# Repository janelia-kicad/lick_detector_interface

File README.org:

# Created 2021-05-14 Fri 12:59
#+OPTIONS: title:nil author:nil email:nil toc:t |:t ^:nil
* Repository Information

- Name :: lick_detector_interface
- Version :: 1.0
- License :: Open-Source Hardware
- URL :: https://github.com/janelia-kicad/lick_detector_interface
- Author :: Peter Polidoro
- Email :: peter@polidoro.io

** Description

This board connects a Teensy 4.1 to 12 lick_detector boards.

* Images

* Schematic

[[file:./schematic/lick_detector_interface.pdf][./schematic/lick_detector_interface.pdf]]

[[file:./schematic/images/schematic00.png]]

[[file:./schematic/images/schematic01.png]]

[[file:./schematic/images/schematic02.png]]

[[file:./schematic/images/schematic03.png]]

[[file:./schematic/images/schematic04.png]]

[[file:./schematic/images/schematic05.png]]

[[file:./schematic/images/schematic06.png]]

[[file:./schematic/images/schematic07.png]]

[[file:./schematic/images/schematic08.png]]

[[file:./schematic/images/schematic09.png]]

[[file:./schematic/images/schematic10.png]]

[[file:./schematic/images/schematic11.png]]

[[file:./schematic/images/schematic12.png]]

* Gerbers

[[file:./gerbers/images/gerbers00.png]]

[[file:./gerbers/images/gerbers01.png]]

* Bill of Materials

** PCB Parts

| Item | Reference(s)                           | Quantity | Manufacturer                 | Manufacturer Part Number | Vendor   | Vendor Part Number | Description                    |
|------+----------------------------------------+----------+------------------------------+--------------------------+----------+--------------------+--------------------------------|
|    1 | P1 P10 P11 P12 P2 P3 P4 P5 P6 P7 P8 P9 |       12 | Molex                        |               0525590853 | Digi-Key | WM6757CT-ND        | CONN FFC VERT 8POS 0.50MM SMD  |
|    2 | TEENSY1                                |       48 | Mill-Max Manufacturing Corp. |  0305-0-15-15-47-27-10-0 | Digi-Key | ED90331-ND         | CONN PIN RCPT .025-.037 SOLDER |
|      | FID1 FID2 FID3 FID4 MH1 MH2 MH3 MH4    |        8 |                              |                          |          |                    |                                |

** Supplemental Parts

| Item | Quantity | Manufacturer | Manufacturer Part Number | Vendor | Vendor Part Number | Description |
|------+----------+--------------+--------------------------+--------+--------------------+-------------|
#+TBLFM: $1=@#-1

** Vendor Parts Lists

[[file:./bom/Digi-Key_parts.csv][./bom/Digi-Key_parts.csv]]

* Supplemental Documentation

** Assembly Instructions

- Solder surface mount and through hole components onto the pcb.

* Manufacturing Archive

Send manufacturing zip file to your favorite PCB manufacturer for fabrication.

[[file:./manufacturing/lick_detector_interface_v1.0.zip][./manufacturing/lick_detector_interface_v1.0.zip]]

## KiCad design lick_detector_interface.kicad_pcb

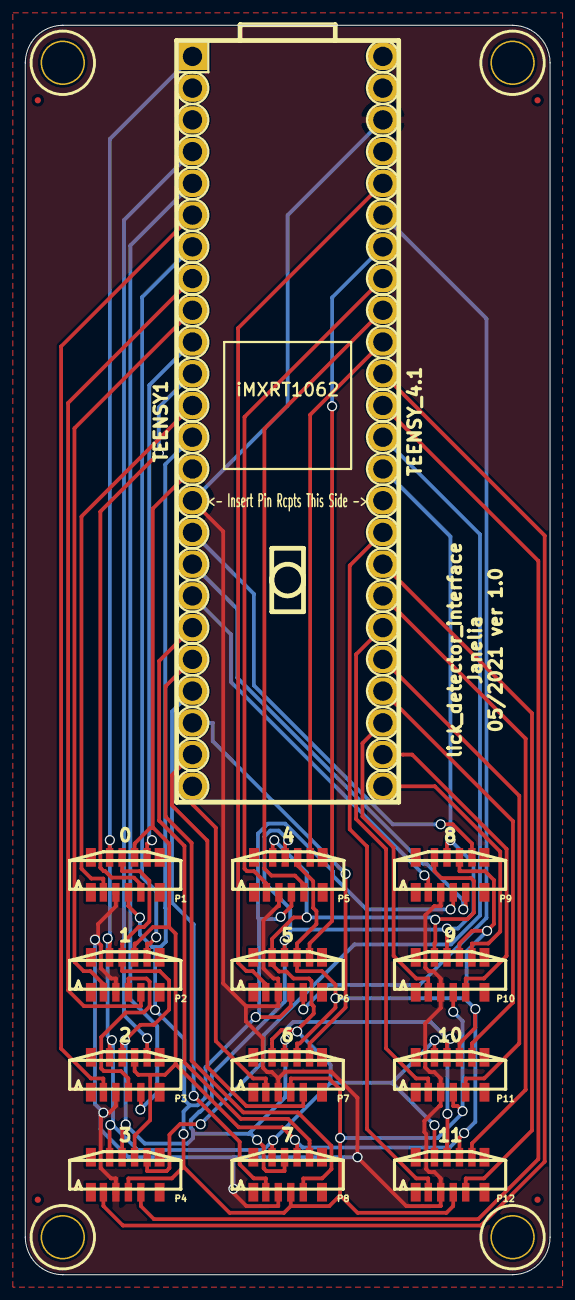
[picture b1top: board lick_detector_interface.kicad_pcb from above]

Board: 2 copper layers, 42.0 x 100.0 mm, 21 parts (0 on the bottom side), 41 nets.

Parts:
FID1, FID2, FID3, FID4: FIDUCIAL
MH1, MH2, MH3, MH4: MOUNTING_HOLE_4-40
P1, P2, P3, P4, P5, P6, P7, P8, P9, P10, P11, P12: CONN_FFC_8_VERT; Molex_FFC_1x8_P0.5mm_Vertical
TEENSY1: TEENSY_4.1

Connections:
/GND: P1.2, P2.2, P3.2, P4.2, P5.2, P6.2, P7.2, P8.2, P9.2, P10.2, P11.2, P12.2, TEENSY1.GND
/INT1_0: P1.8, TEENSY1.8
/INT1_1: P2.8, TEENSY1.5
/INT1_2: P3.8, TEENSY1.2
/INT1_3: P4.8, TEENSY1.14
/INT1_4: P5.8, TEENSY1.17
/INT1_5: P6.8, TEENSY1.20
/INT1_6: P7.8, TEENSY1.30
/INT1_7: P8.8, TEENSY1.27
/INT1_8: P9.8, TEENSY1.24
/INT1_9: P10.8, TEENSY1.33
/INT1_10: P11.8, TEENSY1.36
/INT1_11: P12.8, TEENSY1.39
/INT2_0: P1.7, TEENSY1.9
/INT2_1: P2.7, TEENSY1.6
/INT2_2: P3.7, TEENSY1.3
/INT2_3: P4.7, TEENSY1.15
/INT2_4: P5.7, TEENSY1.18
/INT2_5: P6.7, TEENSY1.21
/INT2_6: P7.7, TEENSY1.31
/INT2_7: P8.7, TEENSY1.28
/INT2_8: P9.7, TEENSY1.25
/INT2_9: P10.7, TEENSY1.34
/INT2_10: P11.7, TEENSY1.37
/INT2_11: P12.7, TEENSY1.40
/MISO: P1.6, P2.6, P3.6, P4.6, P5.6, P6.6, P7.6, P8.6, P9.6, P10.6, P11.6, P12.6, TEENSY1.12
/MOSI: P1.5, P2.5, P3.5, P4.5, P5.5, P6.5, P7.5, P8.5, P9.5, P10.5, P11.5, P12.5, TEENSY1.11
/SCK: P1.4, P2.4, P3.4, P4.4, P5.4, P6.4, P7.4, P8.4, P9.4, P10.4, P11.4, P12.4, TEENSY1.13
/VAA: P1.3, P2.3, P3.3, P4.3, P5.3, P6.3, P7.3, P8.3, P9.3, P10.3, P11.3, P12.3, TEENSY1.3V3
/~CS_0: P1.1, TEENSY1.10
/~CS_1: P2.1, TEENSY1.7
/~CS_2: P3.1, TEENSY1.4
/~CS_3: P4.1, TEENSY1.16
/~CS_4: P5.1, TEENSY1.19
/~CS_5: P6.1, TEENSY1.22
/~CS_6: P7.1, TEENSY1.32
/~CS_7: P8.1, TEENSY1.29
/~CS_8: P9.1, TEENSY1.26
/~CS_9: P10.1, TEENSY1.35
/~CS_10: P11.1, TEENSY1.38
/~CS_11: P12.1, TEENSY1.41

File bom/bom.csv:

Item,Reference(s),Quantity,Manufacturer,Manufacturer Part Number,Vendor,Vendor Part Number,Description
1,P1 P10 P11 P12 P2 P3 P4 P5 P6 P7 P8 P9,12,Molex,0525590853,Digi-Key,WM6757CT-ND,CONN FFC VERT 8POS 0.50MM SMD
2,TEENSY1,48,Mill-Max Manufacturing Corp.,0305-0-15-15-47-27-10-0,Digi-Key,ED90331-ND,CONN PIN RCPT .025-.037 SOLDER
,FID1 FID2 FID3 FID4 MH1 MH2 MH3 MH4,8,,,,,

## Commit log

2021-05-13 lick_detector -> lick_detector_interface
2021-05-13 Add Teensy 4.1
2021-05-14 Finished v1.0
2021-09-16 Update email address
2021-09-17 Update generate_kicad_documentation
2021-09-21 Remove ignored files
2022-02-22 Add guix files
2022-02-23 Add guix documentation
